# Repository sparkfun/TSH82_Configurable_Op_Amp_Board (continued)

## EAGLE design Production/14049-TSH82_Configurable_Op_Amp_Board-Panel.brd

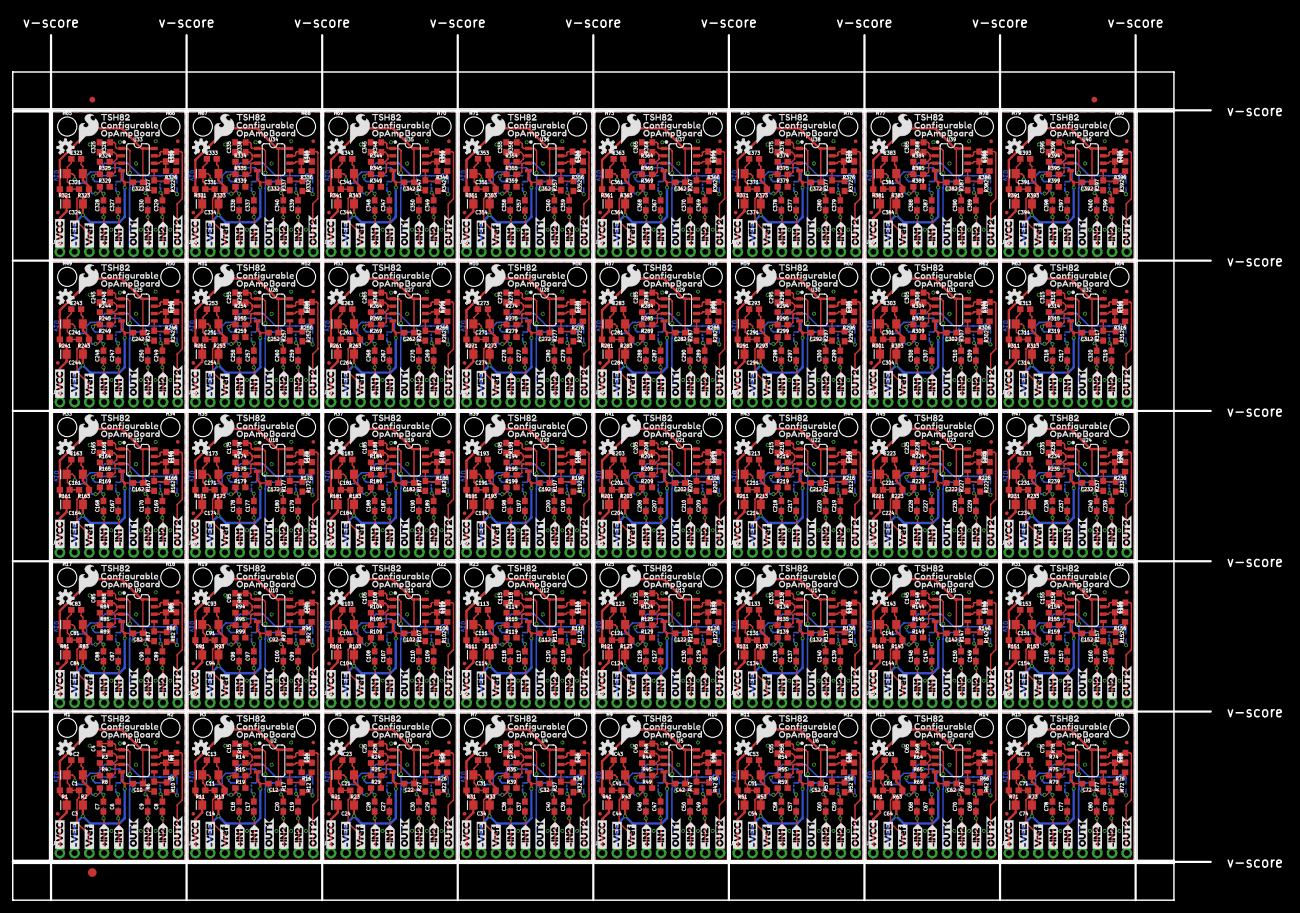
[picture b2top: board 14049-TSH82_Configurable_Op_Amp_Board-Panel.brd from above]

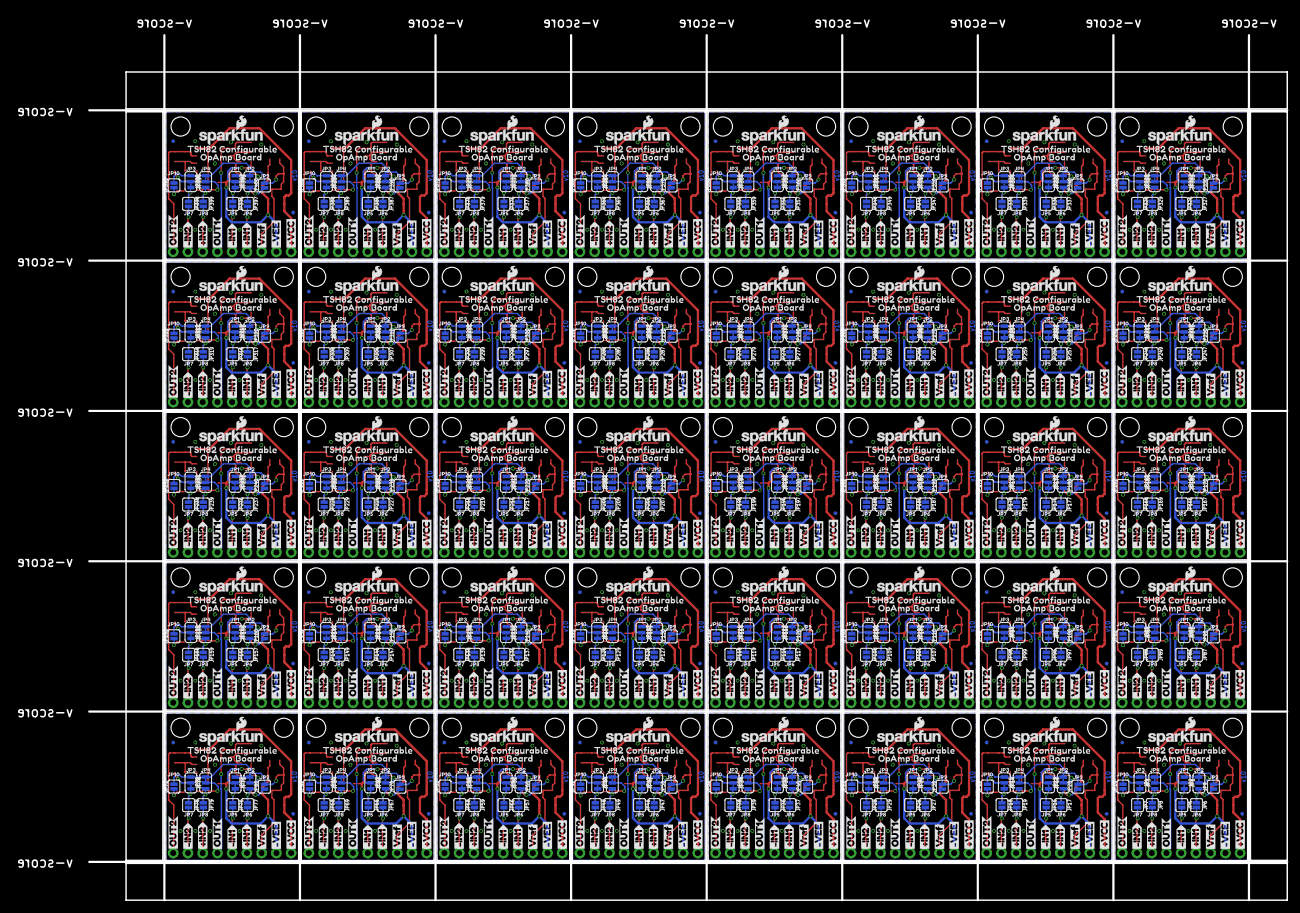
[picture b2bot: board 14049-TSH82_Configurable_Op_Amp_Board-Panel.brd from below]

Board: 2 copper layers, 206.5 x 149.1 mm, 3083 parts (1440 on the bottom side), 920 nets.

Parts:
C1, C3, C11, C14, C21, C24, C31, C34, C41, C44, C51, C54, C61, C64, C71, C74, C81, C84, C91, C94, C101, C104, C111, C114, C121, C124, C131, C134, C141, C144, C151, C154, C161, C164, C171, C174, C181, C184, C191, C194, C201, C204, C211, C214, C221, C224, C231, C234, C241, C244, C251, C254, C261, C264, C271, C274, C281, C284, C291, C294, C301, C304, C311, C314, C321, C324, C331, C334, C341, C344, C351, C354, C361, C364, C371, C374, C381, C384, C391, C394: 10uF; EIA3216
C2, C10, C12, C13, C22, C23, C32, C33, C42, C43, C52, C53, C62, C63, C72, C73, C82, C83, C92, C93, C102, C103, C112, C113, C122, C123, C132, C133, C142, C143, C152, C153, C162, C163, C172, C173, C182, C183, C192, C193, C202, C203, C212, C213, C222, C223, C232, C233, C242, C243, C252, C253, C262, C263, C272, C273, C282, C283, C292, C293, C302, C303, C312, C313, C322, C323, C332, C333, C342, C343, C352, C353, C362, C363, C372, C373, C382, C383, C392, C393: 0.1uF; 0603
C4, C5, C15, C16, C25, C26, C35, C36, C45, C46, C55, C56, C65, C66, C75, C76, C85, C86, C95, C96, C105, C106, C115, C116, C125, C126, C135, C136, C145, C146, C155, C156, C165, C166, C175, C176, C185, C186, C195, C196, C205, C206, C215, C216, C225, C226, C235, C236, C245, C246, C255, C256, C265, C266, C275, C276, C285, C286, C295, C296, C305, C306, C315, C316, C325, C326, C335, C336, C345, C346, C355, C356, C365, C366, C375, C376, C385, C386, C395, C396: DNP; 0603
C6, C7, C8, C9, C17, C18, C19, C20, C27, C28, C29, C30, C37, C38, C39, C40, C47, C48, C49, C50, C57, C58, C59, C60, C67, C68, C69, C70, C77, C78, C79, C80, C87, C88, C89, C90, C97, C98, C99, C100, C107, C108, C109, C110, C117, C118, C119, C120, C127, C128, C129, C130, C137, C138, C139, C140, C147, C148, C149, C150, C157, C158, C159, C160, C167, C168, C169, C170, C177, C178, C179, C180, C187, C188, C189, C190, C197, C198, C199, C200, C207, C208, C209, C210, C217, C218, C219, C220, C227, C228, C229, C230, C237, C238, C239, C240, C247, C248, C249, C250, C257, C258, C259, C260, C267, C268, C269, C270, C277, C278, C279, C280, C287, C288, C289, C290, C297, C298, C299, C300, C307, C308, C309, C310, C317, C318, C319, C320, C327, C328, C329, C330, C337, C338, C339, C340, C347, C348, C349, C350, C357, C358, C359, C360, C367, C368, C369, C370, C377, C378, C379, C380, C387, C388, C389, C390, C397, C398, C399, C400: 1.0uF; 0603
E$1, E$2: FIDUCIAL-1X2
E$3: FIDUCIAL-1.5X3
FD1, FD2, FD3, FD4, FD5, FD6, FD7, FD8, FD9, FD10, FD11, FD12, FD13, FD14, FD15, FD16, FD17, FD18, FD19, FD20, FD21, FD22, FD23, FD24, FD25, FD26, FD27, FD28, FD29, FD30, FD31, FD32, FD33, FD34, FD35, FD36, FD37, FD38, FD39, FD40, FD41, FD42, FD43, FD44, FD45, FD46, FD47, FD48, FD49, FD50, FD51, FD52, FD53, FD54, FD55, FD56, FD57, FD58, FD59, FD60, FD61, FD62, FD63, FD64, FD65, FD66, FD67, FD68, FD69, FD70, FD71, FD72, FD73, FD74, FD75, FD76, FD77, FD78, FD79, FD80, FD81, FD82, FD83, FD84, FD85, FD86, FD87, FD88, FD89, FD90, FD91, FD92, FD93, FD94, FD95, FD96, FD97, FD98, FD99, FD100, FD101, FD102, FD103, FD104, FD105, FD106, FD107, FD108, FD109, FD110, FD111, FD112, FD113, FD114, FD115, FD116, FD117, FD118, FD119, FD120, FD121, FD122, FD123, FD124, FD125, FD126, FD127, FD128, FD129, FD130, FD131, FD132, FD133, FD134, FD135, FD136, FD137, FD138, FD139, FD140, FD141, FD142, FD143, FD144, FD145, FD146, FD147, FD148, FD149, FD150, FD151, FD152, FD153, FD154, FD155, FD156, FD157, FD158, FD159, FD160: FIDUCIALUFIDUCIAL; FIDUCIAL-MICRO
H1, H2, H3, H4, H5, H6, H7, H8, H9, H10, H11, H12, H13, H14, H15, H16, H17, H18, H19, H20, H21, H22, H23, H24, H25, H26, H27, H28, H29, H30, H31, H32, H33, H34, H35, H36, H37, H38, H39, H40, H41, H42, H43, H44, H45, H46, H47, H48, H49, H50, H51, H52, H53, H54, H55, H56, H57, H58, H59, H60, H61, H62, H63, H64, H65, H66, H67, H68, H69, H70, H71, H72, H73, H74, H75, H76, H77, H78, H79, H80: STAND-OFF
J1, J2, J3, J4, J5, J6, J7, J8, J9, J10, J11, J12, J13, J14, J15, J16, J17, J18, J19, J20, J21, J22, J23, J24, J25, J26, J27, J28, J29, J30, J31, J32, J33, J34, J35, J36, J37, J38, J39, J40: 1X09_NO_SILK
JP1, JP2, JP3, JP4, JP11, JP13, JP14, JP15, JP21, JP23, JP24, JP25, JP31, JP33, JP34, JP35, JP41, JP43, JP44, JP45, JP51, JP53, JP54, JP55, JP61, JP63, JP64, JP65, JP71, JP73, JP74, JP75, JP81, JP83, JP84, JP85, JP91, JP93, JP94, JP95, JP101, JP103, JP104, JP105, JP111, JP113, JP114, JP115, JP121, JP123, JP124, JP125, JP131, JP133, JP134, JP135, JP141, JP143, JP144, JP145, JP151, JP153, JP154, JP155, JP161, JP163, JP164, JP165, JP171, JP173, JP174, JP175, JP181, JP183, JP184, JP185, JP191, JP193, JP194, JP195, JP201, JP203, JP204, JP205, JP211, JP213, JP214, JP215, JP221, JP223, JP224, JP225, JP231, JP233, JP234, JP235, JP241, JP243, JP244, JP245, JP251, JP253, JP254, JP255, JP261, JP263, JP264, JP265, JP271, JP273, JP274, JP275, JP281, JP283, JP284, JP285, JP291, JP293, JP294, JP295, JP301, JP303, JP304, JP305, JP311, JP313, JP314, JP315, JP321, JP323, JP324, JP325, JP331, JP333, JP334, JP335, JP341, JP343, JP344, JP345, JP351, JP353, JP354, JP355, JP361, JP363, JP364, JP365, JP371, JP373, JP374, JP375, JP381, JP383, JP384, JP385, JP391, JP393, JP394, JP395: JUMPER-SMT_3_1-NC_TRACE_SILK; SMT-JUMPER_3_1-NC_TRACE_SILK
JP5, JP6, JP7, JP8, JP9, JP10, JP12, JP16, JP17, JP18, JP19, JP20, JP22, JP26, JP27, JP28, JP29, JP30, JP32, JP36, JP37, JP38, JP39, JP40, JP42, JP46, JP47, JP48, JP49, JP50, JP52, JP56, JP57, JP58, JP59, JP60, JP62, JP66, JP67, JP68, JP69, JP70, JP72, JP76, JP77, JP78, JP79, JP80, JP82, JP86, JP87, JP88, JP89, JP90, JP92, JP96, JP97, JP98, JP99, JP100, JP102, JP106, JP107, JP108, JP109, JP110, JP112, JP116, JP117, JP118, JP119, JP120, JP122, JP126, JP127, JP128, JP129, JP130, JP132, JP136, JP137, JP138, JP139, JP140, JP142, JP146, JP147, JP148, JP149, JP150, JP152, JP156, JP157, JP158, JP159, JP160, JP162, JP166, JP167, JP168, JP169, JP170, JP172, JP176, JP177, JP178, JP179, JP180, JP182, JP186, JP187, JP188, JP189, JP190, JP192, JP196, JP197, JP198, JP199, JP200, JP202, JP206, JP207, JP208, JP209, JP210, JP212, JP216, JP217, JP218, JP219, JP220, JP222, JP226, JP227, JP228, JP229, JP230, JP232, JP236, JP237, JP238, JP239, JP240, JP242, JP246, JP247, JP248, JP249, JP250, JP252, JP256, JP257, JP258, JP259, JP260, JP262, JP266, JP267, JP268, JP269, JP270, JP272, JP276, JP277, JP278, JP279, JP280, JP282, JP286, JP287, JP288, JP289, JP290, JP292, JP296, JP297, JP298, JP299, JP300, JP302, JP306, JP307, JP308, JP309, JP310, JP312, JP316, JP317, JP318, JP319, JP320, JP322, JP326, JP327, JP328, JP329, JP330, JP332, JP336, JP337, JP338, JP339, JP340, JP342, JP346, JP347, JP348, JP349, JP350, JP352, JP356, JP357, JP358, JP359, JP360, JP362, JP366, JP367, JP368, JP369, JP370, JP372, JP376, JP377, JP378, JP379, JP380, JP382, JP386, JP387, JP388, JP389, JP390, JP392, JP396, JP397, JP398, JP399, JP400: JUMPER-SMT_2_NO_SILK; SMT-JUMPER_2_NO_SILK
LOGO1, LOGO4, LOGO7, LOGO10, LOGO13, LOGO16, LOGO19, LOGO22, LOGO25, LOGO28, LOGO31, LOGO34, LOGO37, LOGO40, LOGO43, LOGO46, LOGO49, LOGO52, LOGO55, LOGO58, LOGO61, LOGO64, LOGO67, LOGO70, LOGO73, LOGO76, LOGO79, LOGO82, LOGO85, LOGO88, LOGO91, LOGO94, LOGO97, LOGO100, LOGO103, LOGO106, LOGO109, LOGO112, LOGO115, LOGO118: SFE_LOGO_FLAME.2_INCH; SFE_LOGO_FLAME_.2
LOGO2, LOGO5, LOGO8, LOGO11, LOGO14, LOGO17, LOGO20, LOGO23, LOGO26, LOGO29, LOGO32, LOGO35, LOGO38, LOGO41, LOGO44, LOGO47, LOGO50, LOGO53, LOGO56, LOGO59, LOGO62, LOGO65, LOGO68, LOGO71, LOGO74, LOGO77, LOGO80, LOGO83, LOGO86, LOGO89, LOGO92, LOGO95, LOGO98, LOGO101, LOGO104, LOGO107, LOGO110, LOGO113, LOGO116, LOGO119: SFE_LOGO_NAME_FLAME.1_INCH; SFE_LOGO_NAME_FLAME_.1
LOGO3, LOGO6, LOGO9, LOGO12, LOGO15, LOGO18, LOGO21, LOGO24, LOGO27, LOGO30, LOGO33, LOGO36, LOGO39, LOGO42, LOGO45, LOGO48, LOGO51, LOGO54, LOGO57, LOGO60, LOGO63, LOGO66, LOGO69, LOGO72, LOGO75, LOGO78, LOGO81, LOGO84, LOGO87, LOGO90, LOGO93, LOGO96, LOGO99, LOGO102, LOGO105, LOGO108, LOGO111, LOGO114, LOGO117, LOGO120: OSHW-LOGOS; OSHW-LOGO-S
R1, R2, R11, R13, R21, R23, R31, R33, R41, R43, R51, R53, R61, R63, R71, R73, R81, R83, R91, R93, R101, R103, R111, R113, R121, R123, R131, R133, R141, R143, R151, R153, R161, R163, R171, R173, R181, R183, R191, R193, R201, R203, R211, R213, R221, R223, R231, R233, R241, R243, R251, R253, R261, R263, R271, R273, R281, R283, R291, R293, R301, R303, R311, R313, R321, R323, R331, R333, R341, R343, R351, R353, R361, R363, R371, R373, R381, R383, R391, R393: 2.2k; 0603
R3, R4, R5, R6, R14, R15, R16, R17, R24, R25, R26, R27, R34, R35, R36, R37, R44, R45, R46, R47, R54, R55, R56, R57, R64, R65, R66, R67, R74, R75, R76, R77, R84, R85, R86, R87, R94, R95, R96, R97, R104, R105, R106, R107, R114, R115, R116, R117, R124, R125, R126, R127, R134, R135, R136, R137, R144, R145, R146, R147, R154, R155, R156, R157, R164, R165, R166, R167, R174, R175, R176, R177, R184, R185, R186, R187, R194, R195, R196, R197, R204, R205, R206, R207, R214, R215, R216, R217, R224, R225, R226, R227, R234, R235, R236, R237, R244, R245, R246, R247, R254, R255, R256, R257, R264, R265, R266, R267, R274, R275, R276, R277, R284, R285, R286, R287, R294, R295, R296, R297, R304, R305, R306, R307, R314, R315, R316, R317, R324, R325, R326, R327, R334, R335, R336, R337, R344, R345, R346, R347, R354, R355, R356, R357, R364, R365, R366, R367, R374, R375, R376, R377, R384, R385, R386, R387, R394, R395, R396, R397: 10k; 0603
R7, R8, R9, R10, R12, R18, R19, R20, R22, R28, R29, R30, R32, R38, R39, R40, R42, R48, R49, R50, R52, R58, R59, R60, R62, R68, R69, R70, R72, R78, R79, R80, R82, R88, R89, R90, R92, R98, R99, R100, R102, R108, R109, R110, R112, R118, R119, R120, R122, R128, R129, R130, R132, R138, R139, R140, R142, R148, R149, R150, R152, R158, R159, R160, R162, R168, R169, R170, R172, R178, R179, R180, R182, R188, R189, R190, R192, R198, R199, R200, R202, R208, R209, R210, R212, R218, R219, R220, R222, R228, R229, R230, R232, R238, R239, R240, R242, R248, R249, R250, R252, R258, R259, R260, R262, R268, R269, R270, R272, R278, R279, R280, R282, R288, R289, R290, R292, R298, R299, R300, R302, R308, R309, R310, R312, R318, R319, R320, R322, R328, R329, R330, R332, R338, R339, R340, R342, R348, R349, R350, R352, R358, R359, R360, R362, R368, R369, R370, R372, R378, R379, R380, R382, R388, R389, R390, R392, R398, R399, R400: 47k; 0603
U1, U2, U3, U4, U5, U6, U7, U8, U9, U10, U11, U12, U13, U14, U15, U16, U17, U18, U19, U20, U21, U22, U23, U24, U25, U26, U27, U28, U29, U30, U31, U32, U33, U34, U35, U36, U37, U38, U39, U40: TSH82; SO08
U$1, U$2, U$46, U$47, U$82, U$83, U$118, U$119, U$154, U$155, U$190, U$191, U$226, U$227, U$262, U$263, U$298, U$299, U$334, U$335, U$370, U$371, U$406, U$407, U$442, U$443, U$478, U$479, U$514, U$515, U$550, U$551, U$586, U$587, U$622, U$623, U$658, U$659, U$694, U$695, U$730, U$731, U$766, U$767, U$802, U$803, U$838, U$839, U$874, U$875, U$910, U$911, U$946, U$947, U$982, U$983, U$1018, U$1019, U$1054, U$1055, U$1090, U$1091, U$1126, U$1127, U$1162, U$1163, U$1198, U$1199, U$1234, U$1235, U$1270, U$1271, U$1306, U$1307, U$1342, U$1343, U$1378, U$1379, U$1414, U$1415: #VEE1
U$3, U$30, U$45, U$48, U$81, U$84, U$117, U$120, U$153, U$156, U$189, U$192, U$225, U$228, U$261, U$264, U$297, U$300, U$333, U$336, U$369, U$372, U$405, U$408, U$441, U$444, U$477, U$480, U$513, U$516, U$549, U$552, U$585, U$588, U$621, U$624, U$657, U$660, U$693, U$696, U$729, U$732, U$765, U$768, U$801, U$804, U$837, U$840, U$873, U$876, U$909, U$912, U$945, U$948, U$981, U$984, U$1017, U$1020, U$1053, U$1056, U$1089, U$1092, U$1125, U$1128, U$1161, U$1164, U$1197, U$1200, U$1233, U$1236, U$1269, U$1272, U$1305, U$1308, U$1341, U$1344, U$1377, U$1380, U$1413, U$1416: #VCC0
U$4, U$5, U$49, U$50, U$85, U$86, U$121, U$122, U$157, U$158, U$193, U$194, U$229, U$230, U$265, U$266, U$301, U$302, U$337, U$338, U$373, U$374, U$409, U$410, U$445, U$446, U$481, U$482, U$517, U$518, U$553, U$554, U$589, U$590, U$625, U$626, U$661, U$662, U$697, U$698, U$733, U$734, U$769, U$770, U$805, U$806, U$841, U$842, U$877, U$878, U$913, U$914, U$949, U$950, U$985, U$986, U$1021, U$1022, U$1057, U$1058, U$1093, U$1094, U$1129, U$1130, U$1165, U$1166, U$1201, U$1202, U$1237, U$1238, U$1273, U$1274, U$1309, U$1310, U$1345, U$1346, U$1381, U$1382, U$1417, U$1418: VREF6
U$6, U$7, U$51, U$52, U$87, U$88, U$123, U$124, U$159, U$160, U$195, U$196, U$231, U$232, U$267, U$268, U$303, U$304, U$339, U$340, U$375, U$376, U$411, U$412, U$447, U$448, U$483, U$484, U$519, U$520, U$555, U$556, U$591, U$592, U$627, U$628, U$663, U$664, U$699, U$700, U$735, U$736, U$771, U$772, U$807, U$808, U$843, U$844, U$879, U$880, U$915, U$916, U$951, U$952, U$987, U$988, U$1023, U$1024, U$1059, U$1060, U$1095, U$1096, U$1131, U$1132, U$1167, U$1168, U$1203, U$1204, U$1239, U$1240, U$1275, U$1276, U$1311, U$1312, U$1347, U$1348, U$1383, U$1384, U$1419, U$1420: #IN12
U$8, U$9, U$53, U$54, U$89, U$90, U$125, U$126, U$161, U$162, U$197, U$198, U$233, U$234, U$269, U$270, U$305, U$306, U$341, U$342, U$377, U$378, U$413, U$414, U$449, U$450, U$485, U$486, U$521, U$522, U$557, U$558, U$593, U$594, U$629, U$630, U$665, U$666, U$701, U$702, U$737, U$738, U$773, U$774, U$809, U$810, U$845, U$846, U$881, U$882, U$917, U$918, U$953, U$954, U$989, U$990, U$1025, U$1026, U$1061, U$1062, U$1097, U$1098, U$1133, U$1134, U$1169, U$1170, U$1205, U$1206, U$1241, U$1242, U$1277, U$1278, U$1313, U$1314, U$1349, U$1350, U$1385, U$1386, U$1421, U$1422: #IN13
U$10, U$11, U$55, U$56, U$91, U$92, U$127, U$128, U$163, U$164, U$199, U$200, U$235, U$236, U$271, U$272, U$307, U$308, U$343, U$344, U$379, U$380, U$415, U$416, U$451, U$452, U$487, U$488, U$523, U$524, U$559, U$560, U$595, U$596, U$631, U$632, U$667, U$668, U$703, U$704, U$739, U$740, U$775, U$776, U$811, U$812, U$847, U$848, U$883, U$884, U$919, U$920, U$955, U$956, U$991, U$992, U$1027, U$1028, U$1063, U$1064, U$1099, U$1100, U$1135, U$1136, U$1171, U$1172, U$1207, U$1208, U$1243, U$1244, U$1279, U$1280, U$1315, U$1316, U$1351, U$1352, U$1387, U$1388, U$1423, U$1424: OUT17
U$12, U$13, U$57, U$58, U$93, U$94, U$129, U$130, U$165, U$166, U$201, U$202, U$237, U$238, U$273, U$274, U$309, U$310, U$345, U$346, U$381, U$382, U$417, U$418, U$453, U$454, U$489, U$490, U$525, U$526, U$561, U$562, U$597, U$598, U$633, U$634, U$669, U$670, U$705, U$706, U$741, U$742, U$777, U$778, U$813, U$814, U$849, U$850, U$885, U$886, U$921, U$922, U$957, U$958, U$993, U$994, U$1029, U$1030, U$1065, U$1066, U$1101, U$1102, U$1137, U$1138, U$1173, U$1174, U$1209, U$1210, U$1245, U$1246, U$1281, U$1282, U$1317, U$1318, U$1353, U$1354, U$1389, U$1390, U$1425, U$1426: #IN24
U$14, U$16, U$59, U$60, U$95, U$96, U$131, U$132, U$167, U$168, U$203, U$204, U$239, U$240, U$275, U$276, U$311, U$312, U$347, U$348, U$383, U$384, U$419, U$420, U$455, U$456, U$491, U$492, U$527, U$528, U$563, U$564, U$599, U$600, U$635, U$636, U$671, U$672, U$707, U$708, U$743, U$744, U$779, U$780, U$815, U$816, U$851, U$852, U$887, U$888, U$923, U$924, U$959, U$960, U$995, U$996, U$1031, U$1032, U$1067, U$1068, U$1103, U$1104, U$1139, U$1140, U$1175, U$1176, U$1211, U$1212, U$1247, U$1248, U$1283, U$1284, U$1319, U$1320, U$1355, U$1356, U$1391, U$1392, U$1427, U$1428: #IN25
U$15, U$17, U$61, U$62, U$97, U$98, U$133, U$134, U$169, U$170, U$205, U$206, U$241, U$242, U$277, U$278, U$313, U$314, U$349, U$350, U$385, U$386, U$421, U$422, U$457, U$458, U$493, U$494, U$529, U$530, U$565, U$566, U$601, U$602, U$637, U$638, U$673, U$674, U$709, U$710, U$745, U$746, U$781, U$782, U$817, U$818, U$853, U$854, U$889, U$890, U$925, U$926, U$961, U$962, U$997, U$998, U$1033, U$1034, U$1069, U$1070, U$1105, U$1106, U$1141, U$1142, U$1177, U$1178, U$1213, U$1214, U$1249, U$1250, U$1285, U$1286, U$1321, U$1322, U$1357, U$1358, U$1393, U$1394, U$1429, U$1430: OUT28
U$18, U$63, U$99, U$135, U$171, U$207, U$243, U$279, U$315, U$351, U$387, U$423, U$459, U$495, U$531, U$567, U$603, U$639, U$675, U$711, U$747, U$783, U$819, U$855, U$891, U$927, U$963, U$999, U$1035, U$1071, U$1107, U$1143, U$1179, U$1215, U$1251, U$1287, U$1323, U$1359, U$1395, U$1431: JP10
U$19, U$64, U$100, U$136, U$172, U$208, U$244, U$280, U$316, U$352, U$388, U$424, U$460, U$496, U$532, U$568, U$604, U$640, U$676, U$712, U$748, U$784, U$820, U$856, U$892, U$928, U$964, U$1000, U$1036, U$1072, U$1108, U$1144, U$1180, U$1216, U$1252, U$1288, U$1324, U$1360, U$1396, U$1432: JP21
U$20, U$65, U$101, U$137, U$173, U$209, U$245, U$281, U$317, U$353, U$389, U$425, U$461, U$497, U$533, U$569, U$605, U$641, U$677, U$713, U$749, U$785, U$821, U$857, U$893, U$929, U$965, U$1001, U$1037, U$1073, U$1109, U$1145, U$1181, U$1217, U$1253, U$1289, U$1325, U$1361, U$1397, U$1433: JP32
U$21, U$66, U$102, U$138, U$174, U$210, U$246, U$282, U$318, U$354, U$390, U$426, U$462, U$498, U$534, U$570, U$606, U$642, U$678, U$714, U$750, U$786, U$822, U$858, U$894, U$930, U$966, U$1002, U$1038, U$1074, U$1110, U$1146, U$1182, U$1218, U$1254, U$1290, U$1326, U$1362, U$1398, U$1434: JP43
U$22, U$26, U$37, U$41, U$73, U$77, U$109, U$113, U$145, U$149, U$181, U$185, U$217, U$221, U$253, U$257, U$289, U$293, U$325, U$329, U$361, U$365, U$397, U$401, U$433, U$437, U$469, U$473, U$505, U$509, U$541, U$545, U$577, U$581, U$613, U$617, U$649, U$653, U$685, U$689, U$721, U$725, U$757, U$761, U$793, U$797, U$829, U$833, U$865, U$869, U$901, U$905, U$937, U$941, U$973, U$977, U$1009, U$1013, U$1045, U$1049, U$1081, U$1085, U$1117, U$1121, U$1153, U$1157, U$1189, U$1193, U$1225, U$1229, U$1261, U$1265, U$1297, U$1301, U$1333, U$1337, U$1369, U$1373, U$1405, U$1409: TSH820
U$23, U$27, U$38, U$42, U$74, U$78, U$110, U$114, U$146, U$150, U$182, U$186, U$218, U$222, U$254, U$258, U$290, U$294, U$326, U$330, U$362, U$366, U$398, U$402, U$434, U$438, U$470, U$474, U$506, U$510, U$542, U$546, U$578, U$582, U$614, U$618, U$650, U$654, U$686, U$690, U$722, U$726, U$758, U$762, U$794, U$798, U$830, U$834, U$866, U$870, U$902, U$906, U$938, U$942, U$974, U$978, U$1010, U$1014, U$1046, U$1050, U$1082, U$1086, U$1118, U$1122, U$1154, U$1158, U$1190, U$1194, U$1226, U$1230, U$1262, U$1266, U$1298, U$1302, U$1334, U$1338, U$1370, U$1374, U$1406, U$1410: CONFIGURABLE1
U$24, U$28, U$39, U$43, U$75, U$79, U$111, U$115, U$147, U$151, U$183, U$187, U$219, U$223, U$255, U$259, U$291, U$295, U$327, U$331, U$363, U$367, U$399, U$403, U$435, U$439, U$471, U$475, U$507, U$511, U$543, U$547, U$579, U$583, U$615, U$619, U$651, U$655, U$687, U$691, U$723, U$727, U$759, U$763, U$795, U$799, U$831, U$835, U$867, U$871, U$903, U$907, U$939, U$943, U$975, U$979, U$1011, U$1015, U$1047, U$1051, U$1083, U$1087, U$1119, U$1123, U$1155, U$1159, U$1191, U$1195, U$1227, U$1231, U$1263, U$1267, U$1299, U$1303, U$1335, U$1339, U$1371, U$1375, U$1407, U$1411: OPAMP2
U$25, U$29, U$40, U$44, U$76, U$80, U$112, U$116, U$148, U$152, U$184, U$188, U$220, U$224, U$256, U$260, U$292, U$296, U$328, U$332, U$364, U$368, U$400, U$404, U$436, U$440, U$472, U$476, U$508, U$512, U$544, U$548, U$580, U$584, U$616, U$620, U$652, U$656, U$688, U$692, U$724, U$728, U$760, U$764, U$796, U$800, U$832, U$836, U$868, U$872, U$904, U$908, U$940, U$944, U$976, U$980, U$1012, U$1016, U$1048, U$1052, U$1084, U$1088, U$1120, U$1124, U$1156, U$1160, U$1192, U$1196, U$1228, U$1232, U$1264, U$1268, U$1300, U$1304, U$1336, U$1340, U$1372, U$1376, U$1408, U$1412: BOARD3
U$31, U$67, U$103, U$139, U$175, U$211, U$247, U$283, U$319, U$355, U$391, U$427, U$463, U$499, U$535, U$571, U$607, U$643, U$679, U$715, U$751, U$787, U$823, U$859, U$895, U$931, U$967, U$1003, U$1039, U$1075, U$1111, U$1147, U$1183, U$1219, U$1255, U$1291, U$1327, U$1363, U$1399, U$1435: JP54
U$32, U$68, U$104, U$140, U$176, U$212, U$248, U$284, U$320, U$356, U$392, U$428, U$464, U$500, U$536, U$572, U$608, U$644, U$680, U$716, U$752, U$788, U$824, U$860, U$896, U$932, U$968, U$1004, U$1040, U$1076, U$1112, U$1148, U$1184, U$1220, U$1256, U$1292, U$1328, U$1364, U$1400, U$1436: JP65
U$33, U$69, U$105, U$141, U$177, U$213, U$249, U$285, U$321, U$357, U$393, U$429, U$465, U$501, U$537, U$573, U$609, U$645, U$681, U$717, U$753, U$789, U$825, U$861, U$897, U$933, U$969, U$1005, U$1041, U$1077, U$1113, U$1149, U$1185, U$1221, U$1257, U$1293, U$1329, U$1365, U$1401, U$1437: JP76
U$34, U$70, U$106, U$142, U$178, U$214, U$250, U$286, U$322, U$358, U$394, U$430, U$466, U$502, U$538, U$574, U$610, U$646, U$682, U$718, U$754, U$790, U$826, U$862, U$898, U$934, U$970, U$1006, U$1042, U$1078, U$1114, U$1150, U$1186, U$1222, U$1258, U$1294, U$1330, U$1366, U$1402, U$1438: JP87
U$35, U$71, U$107, U$143, U$179, U$215, U$251, U$287, U$323, U$359, U$395, U$431, U$467, U$503, U$539, U$575, U$611, U$647, U$683, U$719, U$755, U$791, U$827, U$863, U$899, U$935, U$971, U$1007, U$1043, U$1079, U$1115, U$1151, U$1187, U$1223, U$1259, U$1295, U$1331, U$1367, U$1403, U$1439: JP98
U$36, U$72, U$108, U$144, U$180, U$216, U$252, U$288, U$324, U$360, U$396, U$432, U$468, U$504, U$540, U$576, U$612, U$648, U$684, U$720, U$756, U$792, U$828, U$864, U$900, U$936, U$972, U$1008, U$1044, U$1080, U$1116, U$1152, U$1188, U$1224, U$1260, U$1296, U$1332, U$1368, U$1404, U$1440: JP109

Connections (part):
+IN1: C7.1, J1.4, JP6.2
+IN2: C9.1, J1.7, JP8.2
+IN3: C18.1, J2.4, JP17.2
+IN4: C20.1, J2.7, JP19.2
+IN5: C28.1, J3.4, JP27.2
+IN6: C30.1, J3.7, JP29.2
+IN7: C38.1, J4.4, JP37.2
+IN8: C40.1, J4.7, JP39.2
+IN9: C48.1, J5.4, JP47.2
+IN10: C50.1, J5.7, JP49.2
+IN11: C58.1, J6.4, JP57.2
+IN12: C60.1, J6.7, JP59.2
+IN13: C68.1, J7.4, JP67.2
+IN14: C70.1, J7.7, JP69.2
+IN15: C78.1, J8.4, JP77.2
+IN16: C80.1, J8.7, JP79.2
+IN17: C88.1, J9.4, JP87.2
+IN18: C90.1, J9.7, JP89.2
+IN19: C98.1, J10.4, JP97.2
+IN20: C100.1, J10.7, JP99.2
+IN21: C108.1, J11.4, JP107.2
+IN22: C110.1, J11.7, JP109.2
+IN23: C118.1, J12.4, JP117.2
+IN24: C120.1, J12.7, JP119.2
+IN25: C128.1, J13.4, JP127.2
+IN26: C130.1, J13.7, JP129.2
+IN27: C138.1, J14.4, JP137.2
+IN28: C140.1, J14.7, JP139.2
+IN29: C148.1, J15.4, JP147.2
+IN30: C150.1, J15.7, JP149.2
+IN31: C158.1, J16.4, JP157.2
+IN32: C160.1, J16.7, JP159.2
+IN33: C168.1, J17.4, JP167.2
+IN34: C170.1, J17.7, JP169.2
+IN35: C178.1, J18.4, JP177.2
+IN36: C180.1, J18.7, JP179.2
+IN37: C188.1, J19.4, JP187.2
+IN38: C190.1, J19.7, JP189.2
+IN39: C198.1, J20.4, JP197.2
+IN40: C200.1, J20.7, JP199.2
+IN41: C208.1, J21.4, JP207.2
+IN42: C210.1, J21.7, JP209.2
+IN43: C218.1, J22.4, JP217.2
+IN44: C220.1, J22.7, JP219.2
+IN45: C228.1, J23.4, JP227.2
+IN46: C230.1, J23.7, JP229.2
+IN47: C238.1, J24.4, JP237.2
+IN48: C240.1, J24.7, JP239.2
+IN49: C248.1, J25.4, JP247.2
+IN50: C250.1, J25.7, JP249.2
+IN51: C258.1, J26.4, JP257.2
+IN52: C260.1, J26.7, JP259.2
+IN53: C268.1, J27.4, JP267.2
+IN54: C270.1, J27.7, JP269.2
+IN55: C278.1, J28.4, JP277.2
+IN56: C280.1, J28.7, JP279.2
+IN57: C288.1, J29.4, JP287.2
+IN58: C290.1, J29.7, JP289.2
+IN59: C298.1, J30.4, JP297.2
+IN60: C300.1, J30.7, JP299.2
+IN61: C308.1, J31.4, JP307.2
+IN62: C310.1, J31.7, JP309.2
+IN63: C318.1, J32.4, JP317.2
+IN64: C320.1, J32.7, JP319.2
+IN65: C328.1, J33.4, JP327.2
+IN66: C330.1, J33.7, JP329.2
+IN67: C338.1, J34.4, JP337.2
+IN68: C340.1, J34.7, JP339.2
+IN69: C348.1, J35.4, JP347.2
+IN70: C350.1, J35.7, JP349.2
+IN71: C358.1, J36.4, JP357.2
+IN72: C360.1, J36.7, JP359.2
+IN73: C368.1, J37.4, JP367.2
+IN74: C370.1, J37.7, JP369.2
+IN75: C378.1, J38.4, JP377.2
+IN76: C380.1, J38.7, JP379.2
+IN77: C388.1, J39.4, JP387.2
+IN78: C390.1, J39.7, JP389.2
+IN79: C398.1, J40.4, JP397.2
+IN80: C400.1, J40.7, JP399.2
-IN1: C6.1, J1.5, JP5.2
-IN2: C8.1, J1.8, JP7.2
-IN3: C17.1, J2.5, JP16.2
-IN4: C19.1, J2.8, JP18.2
-IN5: C27.1, J3.5, JP26.2
-IN6: C29.1, J3.8, JP28.2
-IN7: C37.1, J4.5, JP36.2
-IN8: C39.1, J4.8, JP38.2
-IN9: C47.1, J5.5, JP46.2
-IN10: C49.1, J5.8, JP48.2
-IN11: C57.1, J6.5, JP56.2
-IN12: C59.1, J6.8, JP58.2
-IN13: C67.1, J7.5, JP66.2
-IN14: C69.1, J7.8, JP68.2
-IN15: C77.1, J8.5, JP76.2
-IN16: C79.1, J8.8, JP78.2
-IN17: C87.1, J9.5, JP86.2
-IN18: C89.1, J9.8, JP88.2
-IN19: C97.1, J10.5, JP96.2
-IN20: C99.1, J10.8, JP98.2
-IN21: C107.1, J11.5, JP106.2
-IN22: C109.1, J11.8, JP108.2
-IN23: C117.1, J12.5, JP116.2
-IN24: C119.1, J12.8, JP118.2
-IN25: C127.1, J13.5, JP126.2
-IN26: C129.1, J13.8, JP128.2
-IN27: C137.1, J14.5, JP136.2
-IN28: C139.1, J14.8, JP138.2
-IN29: C147.1, J15.5, JP146.2
-IN30: C149.1, J15.8, JP148.2
-IN31: C157.1, J16.5, JP156.2
-IN32: C159.1, J16.8, JP158.2
-IN33: C167.1, J17.5, JP166.2
-IN34: C169.1, J17.8, JP168.2
-IN35: C177.1, J18.5, JP176.2
-IN36: C179.1, J18.8, JP178.2
-IN37: C187.1, J19.5, JP186.2
-IN38: C189.1, J19.8, JP188.2
-IN39: C197.1, J20.5, JP196.2
-IN40: C199.1, J20.8, JP198.2
-IN41: C207.1, J21.5, JP206.2
-IN42: C209.1, J21.8, JP208.2
-IN43: C217.1, J22.5, JP216.2
-IN44: C219.1, J22.8, JP218.2
-IN45: C227.1, J23.5, JP226.2
-IN46: C229.1, J23.8, JP228.2
-IN47: C237.1, J24.5, JP236.2
-IN48: C239.1, J24.8, JP238.2
-IN49: C247.1, J25.5, JP246.2
-IN50: C249.1, J25.8, JP248.2
-IN51: C257.1, J26.5, JP256.2
-IN52: C259.1, J26.8, JP258.2
-IN53: C267.1, J27.5, JP266.2
-IN54: C269.1, J27.8, JP268.2
-IN55: C277.1, J28.5, JP276.2
-IN56: C279.1, J28.8, JP278.2
-IN57: C287.1, J29.5, JP286.2
-IN58: C289.1, J29.8, JP288.2
-IN59: C297.1, J30.5, JP296.2
-IN60: C299.1, J30.8, JP298.2
-IN61: C307.1, J31.5, JP306.2
-IN62: C309.1, J31.8, JP308.2
-IN63: C317.1, J32.5, JP316.2
-IN64: C319.1, J32.8, JP318.2
-IN65: C327.1, J33.5, JP326.2
-IN66: C329.1, J33.8, JP328.2
-IN67: C337.1, J34.5, JP336.2
-IN68: C339.1, J34.8, JP338.2
-IN69: C347.1, J35.5, JP346.2
-IN70: C349.1, J35.8, JP348.2
-IN71: C357.1, J36.5, JP356.2
-IN72: C359.1, J36.8, JP358.2
-IN73: C367.1, J37.5, JP366.2
-IN74: C369.1, J37.8, JP368.2
-IN75: C377.1, J38.5, JP376.2
-IN76: C379.1, J38.8, JP378.2
-IN77: C387.1, J39.5, JP386.2
-IN78: C389.1, J39.8, JP388.2
-IN79: C397.1, J40.5, JP396.2
-IN80: C399.1, J40.8, JP398.2
unnamed: C4.1, R3.2, R7.1, U1.2
unnamed: R4.2, R8.2, U1.3
unnamed: JP9.1, R8.1
unnamed: JP1.2, R3.1
unnamed: JP2.2, R4.1
unnamed: C6.2, JP1.3, JP5.1
unnamed: C7.2, JP2.1, JP6.1
unnamed: C15.1, R14.2, R18.1, U2.2
unnamed: C8.2, JP3.3, JP7.1
unnamed: JP3.2, R5.1
unnamed: C5.1, R5.2, R9.2, U1.6
unnamed: R15.2, R19.2, U2.3
unnamed: JP20.1, R19.1
unnamed: JP11.2, R14.1
unnamed: JP13.2, R15.1
unnamed: JP4.2, R6.1
unnamed: C9.2, JP4.1, JP8.1
unnamed: C17.2, JP11.3, JP16.1
unnamed: R6.2, R10.1, U1.5
unnamed: JP10.1, R10.2
unnamed: C18.2, JP13.1, JP17.1
unnamed: C19.2, JP14.3, JP18.1
unnamed: JP14.2, R16.1
unnamed: C16.1, R16.2, R20.2, U2.6
unnamed: JP15.2, R17.1
unnamed: C20.2, JP15.1, JP19.1
unnamed: R12.1, R17.2, U2.5
unnamed: JP12.1, R12.2
unnamed: C25.1, R24.2, R28.1, U3.2
unnamed: R25.2, R29.2, U3.3
unnamed: JP30.1, R29.1
unnamed: JP21.2, R24.1
unnamed: JP23.2, R25.1
unnamed: C27.2, JP21.3, JP26.1
unnamed: C28.2, JP23.1, JP27.1
unnamed: C29.2, JP24.3, JP28.1
unnamed: JP24.2, R26.1
unnamed: C26.1, R26.2, R30.2, U3.6
unnamed: JP25.2, R27.1
unnamed: C30.2, JP25.1, JP29.1
unnamed: R22.1, R27.2, U3.5
unnamed: JP22.1, R22.2
unnamed: C35.1, R34.2, R38.1, U4.2
unnamed: R35.2, R39.2, U4.3
unnamed: JP40.1, R39.1
unnamed: JP31.2, R34.1
unnamed: JP33.2, R35.1
unnamed: C37.2, JP31.3, JP36.1
unnamed: C38.2, JP33.1, JP37.1
unnamed: C39.2, JP34.3, JP38.1
unnamed: JP34.2, R36.1
unnamed: C36.1, R36.2, R40.2, U4.6
unnamed: JP35.2, R37.1
unnamed: C40.2, JP35.1, JP39.1
unnamed: R32.1, R37.2, U4.5
unnamed: JP32.1, R32.2
unnamed: C45.1, R44.2, R48.1, U5.2
unnamed: R45.2, R49.2, U5.3
unnamed: JP50.1, R49.1
unnamed: JP41.2, R44.1
unnamed: JP43.2, R45.1
unnamed: C47.2, JP41.3, JP46.1
unnamed: C48.2, JP43.1, JP47.1
unnamed: C49.2, JP44.3, JP48.1
unnamed: JP44.2, R46.1
unnamed: C46.1, R46.2, R50.2, U5.6
unnamed: JP45.2, R47.1
unnamed: C50.2, JP45.1, JP49.1
unnamed: R42.1, R47.2, U5.5
unnamed: JP42.1, R42.2
unnamed: C55.1, R54.2, R58.1, U6.2
unnamed: R55.2, R59.2, U6.3
unnamed: JP60.1, R59.1
unnamed: JP51.2, R54.1
unnamed: JP53.2, R55.1
unnamed: C57.2, JP51.3, JP56.1
unnamed: C58.2, JP53.1, JP57.1
unnamed: C59.2, JP54.3, JP58.1
unnamed: JP54.2, R56.1
unnamed: C56.1, R56.2, R60.2, U6.6
unnamed: JP55.2, R57.1
unnamed: C60.2, JP55.1, JP59.1
unnamed: R52.1, R57.2, U6.5
unnamed: JP52.1, R52.2
unnamed: C65.1, R64.2, R68.1, U7.2
unnamed: R65.2, R69.2, U7.3
unnamed: JP70.1, R69.1
unnamed: JP61.2, R64.1
unnamed: JP63.2, R65.1
unnamed: C67.2, JP61.3, JP66.1
unnamed: C68.2, JP63.1, JP67.1
unnamed: C69.2, JP64.3, JP68.1
unnamed: JP64.2, R66.1
unnamed: C66.1, R66.2, R70.2, U7.6
unnamed: JP65.2, R67.1
unnamed: C70.2, JP65.1, JP69.1
unnamed: R62.1, R67.2, U7.5
unnamed: JP62.1, R62.2
unnamed: C75.1, R74.2, R78.1, U8.2
unnamed: R75.2, R79.2, U8.3
unnamed: JP80.1, R79.1
unnamed: JP71.2, R74.1
unnamed: JP73.2, R75.1
unnamed: C77.2, JP71.3, JP76.1
unnamed: C78.2, JP73.1, JP77.1
unnamed: C79.2, JP74.3, JP78.1
unnamed: JP74.2, R76.1
unnamed: C76.1, R76.2, R80.2, U8.6
unnamed: JP75.2, R77.1
unnamed: C80.2, JP75.1, JP79.1
unnamed: R72.1, R77.2, U8.5
unnamed: JP72.1, R72.2
unnamed: C85.1, R84.2, R88.1, U9.2
unnamed: R85.2, R89.2, U9.3
unnamed: JP90.1, R89.1
unnamed: JP81.2, R84.1
unnamed: JP83.2, R85.1
unnamed: C87.2, JP81.3, JP86.1
unnamed: C88.2, JP83.1, JP87.1
unnamed: C89.2, JP84.3, JP88.1
unnamed: JP84.2, R86.1
unnamed: C86.1, R86.2, R90.2, U9.6
unnamed: JP85.2, R87.1
unnamed: C90.2, JP85.1, JP89.1
unnamed: R82.1, R87.2, U9.5
unnamed: JP82.1, R82.2
unnamed: C95.1, R94.2, R98.1, U10.2
unnamed: R95.2, R99.2, U10.3
unnamed: JP100.1, R99.1
unnamed: JP91.2, R94.1
unnamed: JP93.2, R95.1
unnamed: C97.2, JP91.3, JP96.1
unnamed: C98.2, JP93.1, JP97.1
unnamed: C99.2, JP94.3, JP98.1
unnamed: JP94.2, R96.1
unnamed: C96.1, R96.2, R100.2, U10.6
unnamed: JP95.2, R97.1
unnamed: C100.2, JP95.1, JP99.1
unnamed: R92.1, R97.2, U10.5
unnamed: JP92.1, R92.2
unnamed: C105.1, R104.2, R108.1, U11.2
unnamed: R105.2, R109.2, U11.3
unnamed: JP110.1, R109.1
unnamed: JP101.2, R104.1
unnamed: JP103.2, R105.1
unnamed: C107.2, JP101.3, JP106.1
unnamed: C108.2, JP103.1, JP107.1
unnamed: C109.2, JP104.3, JP108.1
unnamed: JP104.2, R106.1
unnamed: C106.1, R106.2, R110.2, U11.6
unnamed: JP105.2, R107.1
unnamed: C110.2, JP105.1, JP109.1
unnamed: R102.1, R107.2, U11.5
unnamed: JP102.1, R102.2
unnamed: C115.1, R114.2, R118.1, U12.2
unnamed: R115.2, R119.2, U12.3
unnamed: JP120.1, R119.1
unnamed: JP111.2, R114.1
unnamed: JP113.2, R115.1
unnamed: C117.2, JP111.3, JP116.1
unnamed: C118.2, JP113.1, JP117.1
unnamed: C119.2, JP114.3, JP118.1
unnamed: JP114.2, R116.1
unnamed: C116.1, R116.2, R120.2, U12.6
unnamed: JP115.2, R117.1
unnamed: C120.2, JP115.1, JP119.1
unnamed: R112.1, R117.2, U12.5
unnamed: JP112.1, R112.2
unnamed: C125.1, R124.2, R128.1, U13.2
unnamed: R125.2, R129.2, U13.3
unnamed: JP130.1, R129.1
unnamed: JP121.2, R124.1
unnamed: JP123.2, R125.1
unnamed: C127.2, JP121.3, JP126.1
unnamed: C128.2, JP123.1, JP127.1
unnamed: C129.2, JP124.3, JP128.1
unnamed: JP124.2, R126.1
unnamed: C126.1, R126.2, R130.2, U13.6
unnamed: JP125.2, R127.1
unnamed: C130.2, JP125.1, JP129.1
unnamed: R122.1, R127.2, U13.5
unnamed: JP122.1, R122.2
unnamed: C135.1, R134.2, R138.1, U14.2
unnamed: R135.2, R139.2, U14.3
unnamed: JP140.1, R139.1
unnamed: JP131.2, R134.1
unnamed: JP133.2, R135.1
unnamed: C137.2, JP131.3, JP136.1
unnamed: C138.2, JP133.1, JP137.1
unnamed: C139.2, JP134.3, JP138.1
unnamed: JP134.2, R136.1
unnamed: C136.1, R136.2, R140.2, U14.6
unnamed: JP135.2, R137.1
unnamed: C140.2, JP135.1, JP139.1
unnamed: R132.1, R137.2, U14.5
unnamed: JP132.1, R132.2
unnamed: C145.1, R144.2, R148.1, U15.2
unnamed: R145.2, R149.2, U15.3
unnamed: JP150.1, R149.1
unnamed: JP141.2, R144.1
unnamed: JP143.2, R145.1
unnamed: C147.2, JP141.3, JP146.1
unnamed: C148.2, JP143.1, JP147.1
unnamed: C149.2, JP144.3, JP148.1
unnamed: JP144.2, R146.1
unnamed: C146.1, R146.2, R150.2, U15.6
unnamed: JP145.2, R147.1
unnamed: C150.2, JP145.1, JP149.1
unnamed: R142.1, R147.2, U15.5
unnamed: JP142.1, R142.2
unnamed: C155.1, R154.2, R158.1, U16.2
unnamed: R155.2, R159.2, U16.3
unnamed: JP160.1, R159.1
unnamed: JP151.2, R154.1
unnamed: JP153.2, R155.1
unnamed: C157.2, JP151.3, JP156.1
unnamed: C158.2, JP153.1, JP157.1
unnamed: C159.2, JP154.3, JP158.1
unnamed: JP154.2, R156.1
unnamed: C156.1, R156.2, R160.2, U16.6
unnamed: JP155.2, R157.1
unnamed: C160.2, JP155.1, JP159.1
unnamed: R152.1, R157.2, U16.5
unnamed: JP152.1, R152.2
unnamed: C165.1, R164.2, R168.1, U17.2
unnamed: R165.2, R169.2, U17.3
unnamed: JP170.1, R169.1
unnamed: JP161.2, R164.1
unnamed: JP163.2, R165.1
unnamed: C167.2, JP161.3, JP166.1
unnamed: C168.2, JP163.1, JP167.1
unnamed: C169.2, JP164.3, JP168.1
unnamed: JP164.2, R166.1
unnamed: C166.1, R166.2, R170.2, U17.6
unnamed: JP165.2, R167.1
unnamed: C170.2, JP165.1, JP169.1
unnamed: R162.1, R167.2, U17.5
unnamed: JP162.1, R162.2
unnamed: C175.1, R174.2, R178.1, U18.2
unnamed: R175.2, R179.2, U18.3
unnamed: JP180.1, R179.1
unnamed: JP171.2, R174.1
unnamed: JP173.2, R175.1
unnamed: C177.2, JP171.3, JP176.1
unnamed: C178.2, JP173.1, JP177.1
unnamed: C179.2, JP174.3, JP178.1
unnamed: JP174.2, R176.1
unnamed: C176.1, R176.2, R180.2, U18.6
unnamed: JP175.2, R177.1
unnamed: C180.2, JP175.1, JP179.1
unnamed: R172.1, R177.2, U18.5
unnamed: JP172.1, R172.2
unnamed: C185.1, R184.2, R188.1, U19.2
unnamed: R185.2, R189.2, U19.3
unnamed: JP190.1, R189.1
unnamed: JP181.2, R184.1
unnamed: JP183.2, R185.1
unnamed: C187.2, JP181.3, JP186.1
unnamed: C188.2, JP183.1, JP187.1
unnamed: C189.2, JP184.3, JP188.1
unnamed: JP184.2, R186.1
unnamed: C186.1, R186.2, R190.2, U19.6
unnamed: JP185.2, R187.1
unnamed: C190.2, JP185.1, JP189.1
unnamed: R182.1, R187.2, U19.5
unnamed: JP182.1, R182.2
unnamed: C195.1, R194.2, R198.1, U20.2
unnamed: R195.2, R199.2, U20.3
unnamed: JP200.1, R199.1
unnamed: JP191.2, R194.1
unnamed: JP193.2, R195.1
unnamed: C197.2, JP191.3, JP196.1
unnamed: C198.2, JP193.1, JP197.1
unnamed: C199.2, JP194.3, JP198.1
unnamed: JP194.2, R196.1
unnamed: C196.1, R196.2, R200.2, U20.6
unnamed: JP195.2, R197.1
unnamed: C200.2, JP195.1, JP199.1
unnamed: R192.1, R197.2, U20.5
unnamed: JP192.1, R192.2
unnamed: C205.1, R204.2, R208.1, U21.2
unnamed: R205.2, R209.2, U21.3
unnamed: JP210.1, R209.1
unnamed: JP201.2, R204.1
unnamed: JP203.2, R205.1
unnamed: C207.2, JP201.3, JP206.1
unnamed: C208.2, JP203.1, JP207.1
unnamed: C209.2, JP204.3, JP208.1
unnamed: JP204.2, R206.1
unnamed: C206.1, R206.2, R210.2, U21.6
unnamed: JP205.2, R207.1
unnamed: C210.2, JP205.1, JP209.1
unnamed: R202.1, R207.2, U21.5
unnamed: JP202.1, R202.2
unnamed: C215.1, R214.2, R218.1, U22.2
unnamed: R215.2, R219.2, U22.3
unnamed: JP220.1, R219.1
unnamed: JP211.2, R214.1
unnamed: JP213.2, R215.1
unnamed: C217.2, JP211.3, JP216.1
unnamed: C218.2, JP213.1, JP217.1
unnamed: C219.2, JP214.3, JP218.1
unnamed: JP214.2, R216.1
unnamed: C216.1, R216.2, R220.2, U22.6
unnamed: JP215.2, R217.1
unnamed: C220.2, JP215.1, JP219.1
unnamed: R212.1, R217.2, U22.5
unnamed: JP212.1, R212.2
unnamed: C225.1, R224.2, R228.1, U23.2
unnamed: R225.2, R229.2, U23.3
unnamed: JP230.1, R229.1
unnamed: JP221.2, R224.1
unnamed: JP223.2, R225.1
unnamed: C227.2, JP221.3, JP226.1
unnamed: C228.2, JP223.1, JP227.1
unnamed: C229.2, JP224.3, JP228.1
unnamed: JP224.2, R226.1
unnamed: C226.1, R226.2, R230.2, U23.6
unnamed: JP225.2, R227.1
unnamed: C230.2, JP225.1, JP229.1
unnamed: R222.1, R227.2, U23.5
unnamed: JP222.1, R222.2
unnamed: C235.1, R234.2, R238.1, U24.2
unnamed: R235.2, R239.2, U24.3
unnamed: JP240.1, R239.1
unnamed: JP231.2, R234.1
unnamed: JP233.2, R235.1
unnamed: C237.2, JP231.3, JP236.1
unnamed: C238.2, JP233.1, JP237.1
unnamed: C239.2, JP234.3, JP238.1
unnamed: JP234.2, R236.1
unnamed: C236.1, R236.2, R240.2, U24.6
unnamed: JP235.2, R237.1
unnamed: C240.2, JP235.1, JP239.1
unnamed: R232.1, R237.2, U24.5
unnamed: JP232.1, R232.2
unnamed: C245.1, R244.2, R248.1, U25.2
unnamed: R245.2, R249.2, U25.3
unnamed: JP250.1, R249.1
unnamed: JP241.2, R244.1
unnamed: JP243.2, R245.1
unnamed: C247.2, JP241.3, JP246.1
unnamed: C248.2, JP243.1, JP247.1
unnamed: C249.2, JP244.3, JP248.1
unnamed: JP244.2, R246.1
unnamed: C246.1, R246.2, R250.2, U25.6
unnamed: JP245.2, R247.1
unnamed: C250.2, JP245.1, JP249.1
unnamed: R242.1, R247.2, U25.5
unnamed: JP242.1, R242.2
unnamed: C255.1, R254.2, R258.1, U26.2
unnamed: R255.2, R259.2, U26.3
unnamed: JP260.1, R259.1
unnamed: JP251.2, R254.1
unnamed: JP253.2, R255.1
unnamed: C257.2, JP251.3, JP256.1
unnamed: C258.2, JP253.1, JP257.1
unnamed: C259.2, JP254.3, JP258.1
unnamed: JP254.2, R256.1
unnamed: C256.1, R256.2, R260.2, U26.6
unnamed: JP255.2, R257.1
unnamed: C260.2, JP255.1, JP259.1
unnamed: R252.1, R257.2, U26.5
unnamed: JP252.1, R252.2
unnamed: C265.1, R264.2, R268.1, U27.2
unnamed: R265.2, R269.2, U27.3
unnamed: JP270.1, R269.1
unnamed: JP261.2, R264.1
unnamed: JP263.2, R265.1
unnamed: C267.2, JP261.3, JP266.1
unnamed: C268.2, JP263.1, JP267.1
unnamed: C269.2, JP264.3, JP268.1
unnamed: JP264.2, R266.1
unnamed: C266.1, R266.2, R270.2, U27.6
unnamed: JP265.2, R267.1
unnamed: C270.2, JP265.1, JP269.1
unnamed: R262.1, R267.2, U27.5
unnamed: JP262.1, R262.2
unnamed: C275.1, R274.2, R278.1, U28.2
unnamed: R275.2, R279.2, U28.3
unnamed: JP280.1, R279.1
unnamed: JP271.2, R274.1
unnamed: JP273.2, R275.1
unnamed: C277.2, JP271.3, JP276.1
unnamed: C278.2, JP273.1, JP277.1
unnamed: C279.2, JP274.3, JP278.1
unnamed: JP274.2, R276.1
unnamed: C276.1, R276.2, R280.2, U28.6
unnamed: JP275.2, R277.1
unnamed: C280.2, JP275.1, JP279.1
unnamed: R272.1, R277.2, U28.5
unnamed: JP272.1, R272.2
unnamed: C285.1, R284.2, R288.1, U29.2
unnamed: R285.2, R289.2, U29.3
unnamed: JP290.1, R289.1
unnamed: JP281.2, R284.1
unnamed: JP283.2, R285.1
unnamed: C287.2, JP281.3, JP286.1
unnamed: C288.2, JP283.1, JP287.1
unnamed: C289.2, JP284.3, JP288.1
unnamed: JP284.2, R286.1
unnamed: C286.1, R286.2, R290.2, U29.6
unnamed: JP285.2, R287.1
unnamed: C290.2, JP285.1, JP289.1
unnamed: R282.1, R287.2, U29.5
unnamed: JP282.1, R282.2
unnamed: C295.1, R294.2, R298.1, U30.2
unnamed: R295.2, R299.2, U30.3
unnamed: JP300.1, R299.1
unnamed: JP291.2, R294.1
unnamed: JP293.2, R295.1
unnamed: C297.2, JP291.3, JP296.1
unnamed: C298.2, JP293.1, JP297.1
unnamed: C299.2, JP294.3, JP298.1
unnamed: JP294.2, R296.1
unnamed: C296.1, R296.2, R300.2, U30.6
unnamed: JP295.2, R297.1
unnamed: C300.2, JP295.1, JP299.1
unnamed: R292.1, R297.2, U30.5
unnamed: JP292.1, R292.2
unnamed: C305.1, R304.2, R308.1, U31.2
unnamed: R305.2, R309.2, U31.3
unnamed: JP310.1, R309.1
unnamed: JP301.2, R304.1
unnamed: JP303.2, R305.1
unnamed: C307.2, JP301.3, JP306.1
unnamed: C308.2, JP303.1, JP307.1
unnamed: C309.2, JP304.3, JP308.1
unnamed: JP304.2, R306.1
unnamed: C306.1, R306.2, R310.2, U31.6
unnamed: JP305.2, R307.1
unnamed: C310.2, JP305.1, JP309.1
unnamed: R302.1, R307.2, U31.5
unnamed: JP302.1, R302.2
unnamed: C315.1, R314.2, R318.1, U32.2
unnamed: R315.2, R319.2, U32.3
unnamed: JP320.1, R319.1
unnamed: JP311.2, R314.1
unnamed: JP313.2, R315.1
unnamed: C317.2, JP311.3, JP316.1
unnamed: C318.2, JP313.1, JP317.1
unnamed: C319.2, JP314.3, JP318.1
unnamed: JP314.2, R316.1
unnamed: C316.1, R316.2, R320.2, U32.6
unnamed: JP315.2, R317.1
unnamed: C320.2, JP315.1, JP319.1
unnamed: R312.1, R317.2, U32.5
unnamed: JP312.1, R312.2
unnamed: C325.1, R324.2, R328.1, U33.2
unnamed: R325.2, R329.2, U33.3
unnamed: JP330.1, R329.1
unnamed: JP321.2, R324.1
unnamed: JP323.2, R325.1
unnamed: C327.2, JP321.3, JP326.1
unnamed: C328.2, JP323.1, JP327.1
unnamed: C329.2, JP324.3, JP328.1
unnamed: JP324.2, R326.1
unnamed: C326.1, R326.2, R330.2, U33.6
unnamed: JP325.2, R327.1
unnamed: C330.2, JP325.1, JP329.1
unnamed: R322.1, R327.2, U33.5
unnamed: JP322.1, R322.2
unnamed: C335.1, R334.2, R338.1, U34.2
unnamed: R335.2, R339.2, U34.3
unnamed: JP340.1, R339.1
unnamed: JP331.2, R334.1
unnamed: JP333.2, R335.1
unnamed: C337.2, JP331.3, JP336.1
unnamed: C338.2, JP333.1, JP337.1
unnamed: C339.2, JP334.3, JP338.1
unnamed: JP334.2, R336.1
unnamed: C336.1, R336.2, R340.2, U34.6
unnamed: JP335.2, R337.1
unnamed: C340.2, JP335.1, JP339.1
unnamed: R332.1, R337.2, U34.5
unnamed: JP332.1, R332.2
unnamed: C345.1, R344.2, R348.1, U35.2
unnamed: R345.2, R349.2, U35.3
unnamed: JP350.1, R349.1
unnamed: JP341.2, R344.1
unnamed: JP343.2, R345.1
unnamed: C347.2, JP341.3, JP346.1
unnamed: C348.2, JP343.1, JP347.1
unnamed: C349.2, JP344.3, JP348.1
unnamed: JP344.2, R346.1
unnamed: C346.1, R346.2, R350.2, U35.6
unnamed: JP345.2, R347.1
unnamed: C350.2, JP345.1, JP349.1
unnamed: R342.1, R347.2, U35.5
unnamed: JP342.1, R342.2
unnamed: C355.1, R354.2, R358.1, U36.2
unnamed: R355.2, R359.2, U36.3
unnamed: JP360.1, R359.1
unnamed: JP351.2, R354.1
unnamed: JP353.2, R355.1
unnamed: C357.2, JP351.3, JP356.1
unnamed: C358.2, JP353.1, JP357.1
unnamed: C359.2, JP354.3, JP358.1
unnamed: JP354.2, R356.1
unnamed: C356.1, R356.2, R360.2, U36.6
unnamed: JP355.2, R357.1
unnamed: C360.2, JP355.1, JP359.1
unnamed: R352.1, R357.2, U36.5
unnamed: JP352.1, R352.2
unnamed: C365.1, R364.2, R368.1, U37.2
unnamed: R365.2, R369.2, U37.3
unnamed: JP370.1, R369.1
unnamed: JP361.2, R364.1
unnamed: JP363.2, R365.1
unnamed: C367.2, JP361.3, JP366.1
unnamed: C368.2, JP363.1, JP367.1
unnamed: C369.2, JP364.3, JP368.1
unnamed: JP364.2, R366.1
unnamed: C366.1, R366.2, R370.2, U37.6
unnamed: JP365.2, R367.1
unnamed: C370.2, JP365.1, JP369.1
unnamed: R362.1, R367.2, U37.5
unnamed: JP362.1, R362.2
unnamed: C375.1, R374.2, R378.1, U38.2
unnamed: R375.2, R379.2, U38.3
unnamed: JP380.1, R379.1
unnamed: JP371.2, R374.1
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
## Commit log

2018-06-08 Schematic done, in the middle of layout.
2018-07-05 Close to done, labels, layout, etc.
2018-07-18 Ready for review.
2018-07-23 Changes post design review.
2018-08-20 Pushed the power trace out a bit and added some ground vias.
2018-08-23 Add bottom fiducials, move a trace, increment version, remove extra files.
2018-09-11 created panel v10
2018-11-01 Update ReadMe
    Empty file - updating to match repo template
